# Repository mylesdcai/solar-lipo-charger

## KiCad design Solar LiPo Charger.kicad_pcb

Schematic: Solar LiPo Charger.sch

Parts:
C1: 2.2u; 1206
C2, C3, C7, C11: 1u; 0805
C4, C5, C12: 10u; 1206
C6, C8, C9, C10: 0.1u; 0805
C13: 4.7u; 1206
C14: 22p; 0805
D1: SSB43L; SSB43L-E3&slash_52T
D2: RED; LED_0603_1608Metric
D3: GREEN; LED_0603_1608Metric
D4: BAT54C-7-F; SOT-23-3
J1: Barrel_Jack; BarrelJack_CUI_PJ-102AH_Horizontal
J2: Screw_Terminal_01x02; TerminalBlock_4Ucon_1x02_P3.50mm_Horizontal
L1: 10uH; NR8040T100M
Q1, Q2: DMN3404L-7; SOT-23-3
R1, R7: 2; 0805
R2: 39.2k; 0805
R3: 10k; 0805
R4: 10; 0805
R5, R6: 2k; 0805
R8: 2.15k; 0805
R9: 6.04k; 0805
R10: 10k NTC; 0805
R11: .02; 1206
R12, R13: 100k; 0805
U1: bq24650; BQ24650RVAT

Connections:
BTST: C6.1, D4.1 (K), L1.1, Q1.3 (S), Q2.1 (D), U1.14
GND: C1.2, C2.2, C3.2, C4.2, C5.2, C7.2, C8.1, C10.1, C11.1, C12.2, C13.2, J1.2, J2.2, Q2.3 (S), R3.2, R9.2, R10.2, R13.2, U1.11
MPPSET: R2.2, R3.1, U1.2
unnamed: C1.1, R1.2
unnamed: C2.1, R4.2, U1.1
unnamed: C3.1, C4.1, C5.1, D1.1 (K), Q1.1 (D), R4.1
unnamed: C6.2, U1.16
unnamed: C7.1, U1.6
unnamed: C11.2, D4.2 (A), U1.12
unnamed: D2.1 (K), U1.3
unnamed: D2.2 (A), R5.1
unnamed: D3.1 (K), U1.5
unnamed: D3.2 (A), R6.1
unnamed: Q1.2 (G), R7.1
unnamed: Q2.2 (G), U1.13
unnamed: R7.2, U1.15
unnamed: R8.1, U1.7
SRN: C8.2, C9.2, C12.1, C13.1, C14.1, J2.1, R11.1, R12.1, U1.9
SRP: C9.1, C10.2, L1.2, R11.2, U1.10
TS: R8.2, R9.1, R10.1, U1.4
VFB: C14.2, R12.2, R13.1, U1.8
Vsolar: D1.2 (A), J1.1, R1.1, R2.1, R5.2, R6.2

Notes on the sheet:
Input Filter
Gate Resistor
Input Capacitors
Rsense
Output Capacitors

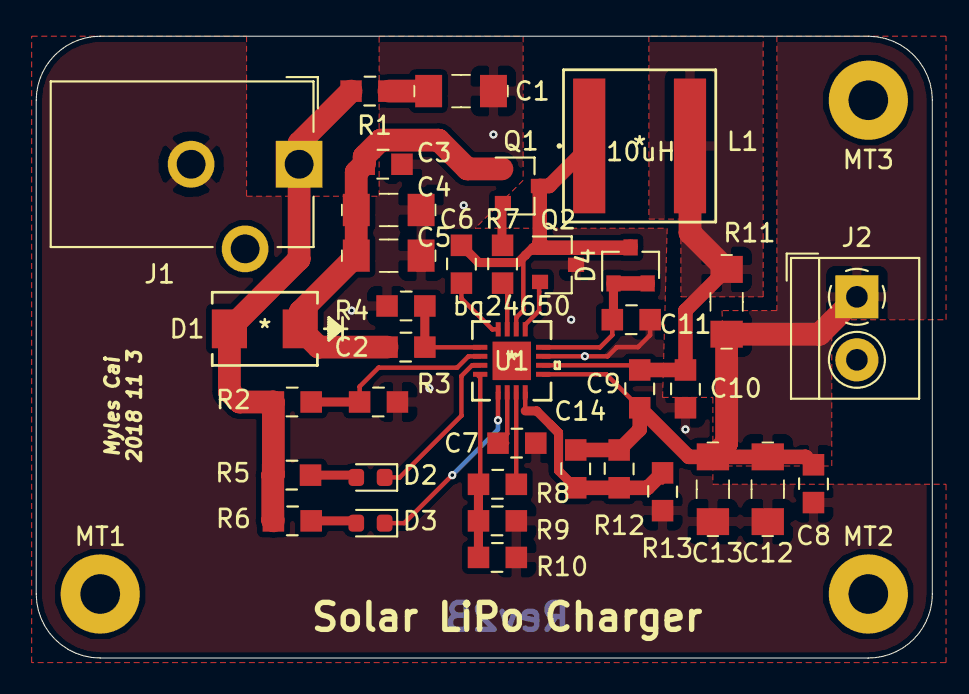
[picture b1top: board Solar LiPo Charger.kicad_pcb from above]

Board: 2 copper layers, 49.8 x 34.5 mm, 40 parts (0 on the bottom side), 22 nets.

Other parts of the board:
MT1, MT2, MT3: MountingHole_2.2mm_M2_Pad

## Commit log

2018-11-04 initial
2018-11-04 Rev2B Layout
2018-11-04 Rev2B Final
2018-11-04 rounded edges
2018-11-04 moved input filt

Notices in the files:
parts and their libraries:
Copyright 2016 Accelerated Designs. All rights reserved.
